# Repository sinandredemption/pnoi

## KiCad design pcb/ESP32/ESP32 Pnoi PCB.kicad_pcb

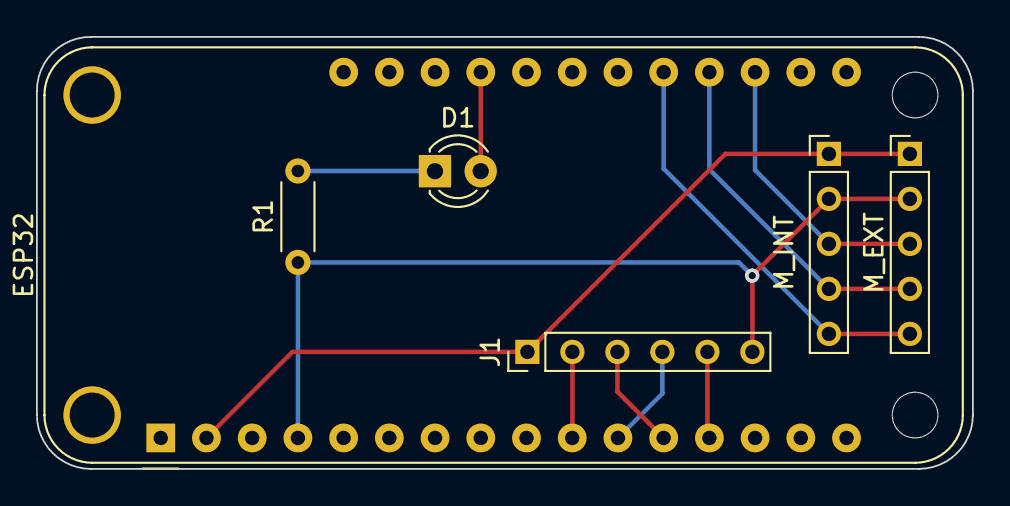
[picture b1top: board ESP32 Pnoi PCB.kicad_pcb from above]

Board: 2 copper layers, 52.0 x 24.0 mm, 6 parts (0 on the bottom side), 11 nets.

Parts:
D1: LED; LED_D3.0mm
ESP32: Adafruit_Feather_HUZZAH32_ESP32; Adafruit_Feather_WithMountingHoles
J1: SD_Card; 6-Pin SD Card Connector
M_EXT: M_EXT; 5-Pin MEMS Connector
M_INT: M_INT; 5-Pin MEMS Connector
R1: 330; R_Axial_DIN0204_L3.6mm_D1.6mm_P5.08mm_Horizontal

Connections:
GND: ESP32.4 (GND), J1.GND, M_EXT.GND, M_INT.GND, R1.1
unnamed: D1.1 (K), R1.2
unnamed: D1.2 (A), ESP32.25 (A12/IO13)
unnamed: ESP32.10 (IO4/A5), J1.CS
unnamed: ESP32.11 (SCK/IO5), J1.CLK
unnamed: ESP32.12 (MOSI/IO18), J1.MOSI
unnamed: ESP32.13 (MISO/IO19), J1.MISO
unnamed: ESP32.19 (A6/IO14), M_EXT.BCLK, M_INT.BCLK
unnamed: ESP32.20 (A7/IO32), M_EXT.DOUT, M_INT.DOUT
unnamed: ESP32.21 (A8/IO15), M_EXT.LRCL, M_INT.LRCL
VCC: ESP32.2 (3V3), J1.3v3, M_EXT.3V, M_INT.3V

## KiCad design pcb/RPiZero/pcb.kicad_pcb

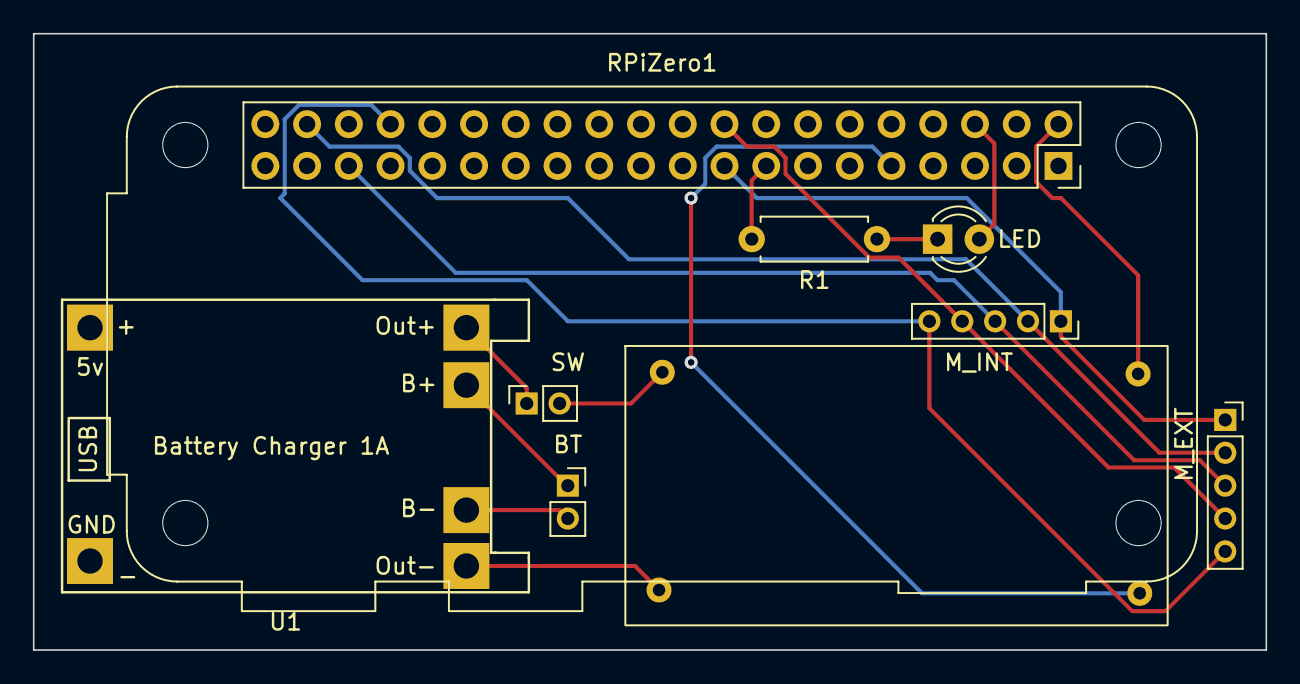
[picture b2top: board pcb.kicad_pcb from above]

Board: 2 copper layers, 75.0 x 37.5 mm, 9 parts (0 on the bottom side), 15 nets.

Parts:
BT: Battery_Cell; PinSocket_1x02_P2.00mm_Vertical
LED: LED; LED_D3.0mm
M_EXT: Conn_01x05_Female; PinSocket_1x05_P2.00mm_Vertical
M_INT: Conn_01x05_Female; PinSocket_1x05_P2.00mm_Vertical
R1: R_US; R_Axial_DIN0207_L6.3mm_D2.5mm_P7.62mm_Horizontal
RPiZero1: RPi_GPIO; Raspberry_Pi_Zero_Socketed_THT_FaceDown_MountingHoles
SW: M2011S3AW03; PinSocket_1x02_P2.00mm_Vertical
U: GENERIC_BUCK_CONV
U1: TP4056

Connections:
unnamed: BT.1 (+), U1.5 (B+)
unnamed: BT.2 (-), U1.6 (B-)
unnamed: LED.1 (K), R1.2
unnamed: LED.2 (A), RPiZero1.6 (GND)
unnamed: M_EXT.1, M_INT.1, RPiZero1.17 (3.3V)
unnamed: M_EXT.2, M_INT.2, RPiZero1.38 (GPIO20)
unnamed: M_EXT.3, M_INT.3, RPiZero1.35 (GPIO19)
unnamed: M_EXT.4, M_INT.4, RPiZero1.18 (GPIO24)
unnamed: M_EXT.5, M_INT.5, RPiZero1.34 (GND)
unnamed: R1.1, RPiZero1.15 (GPIO22)
unnamed: RPiZero1.2 (5V), U.3 (OUT+)
unnamed: RPiZero1.9 (GND), U.4 (OUT-)
unnamed: SW.1 (A), U1.3 (Out+)
unnamed: SW.2 (B), U.1 (VIN+)
unnamed: U.2 (VIN-), U1.4 (Out-)

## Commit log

2022-01-25 Create unified repo for all Pnoi projects
2022-02-24 Add PCB design and ESP32 server code
2022-02-26 Add new folder for ESP32 PCB
2022-02-26 Renaming
2022-02-26 Complete ESP32 PCB
